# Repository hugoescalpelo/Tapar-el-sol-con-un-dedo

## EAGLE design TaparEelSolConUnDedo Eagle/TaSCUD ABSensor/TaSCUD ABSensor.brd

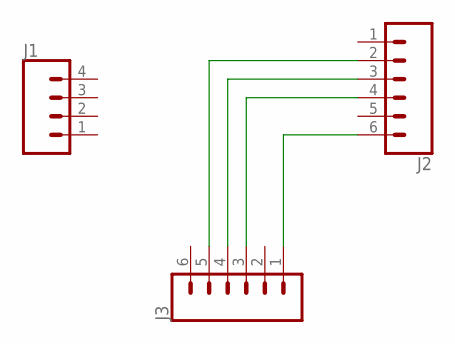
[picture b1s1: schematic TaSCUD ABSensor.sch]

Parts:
J1: CONN_04LONGPADS; 1X04_LONGPADS
J2, J3: CONN_06LONGPADS; 1X06_LONGPADS

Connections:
unnamed: J2.6, J3.1
unnamed: J2.4, J3.3
unnamed: J2.3, J3.4
unnamed: J2.2, J3.5

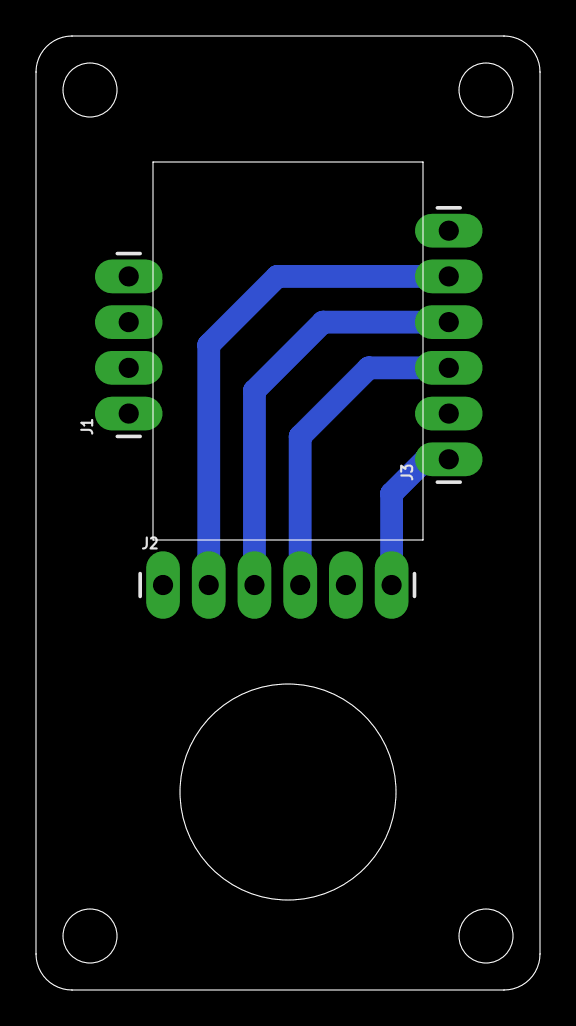
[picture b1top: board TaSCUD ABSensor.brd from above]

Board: 2 copper layers, 28.0 x 53.0 mm, 3 parts (0 on the bottom side), 4 nets.

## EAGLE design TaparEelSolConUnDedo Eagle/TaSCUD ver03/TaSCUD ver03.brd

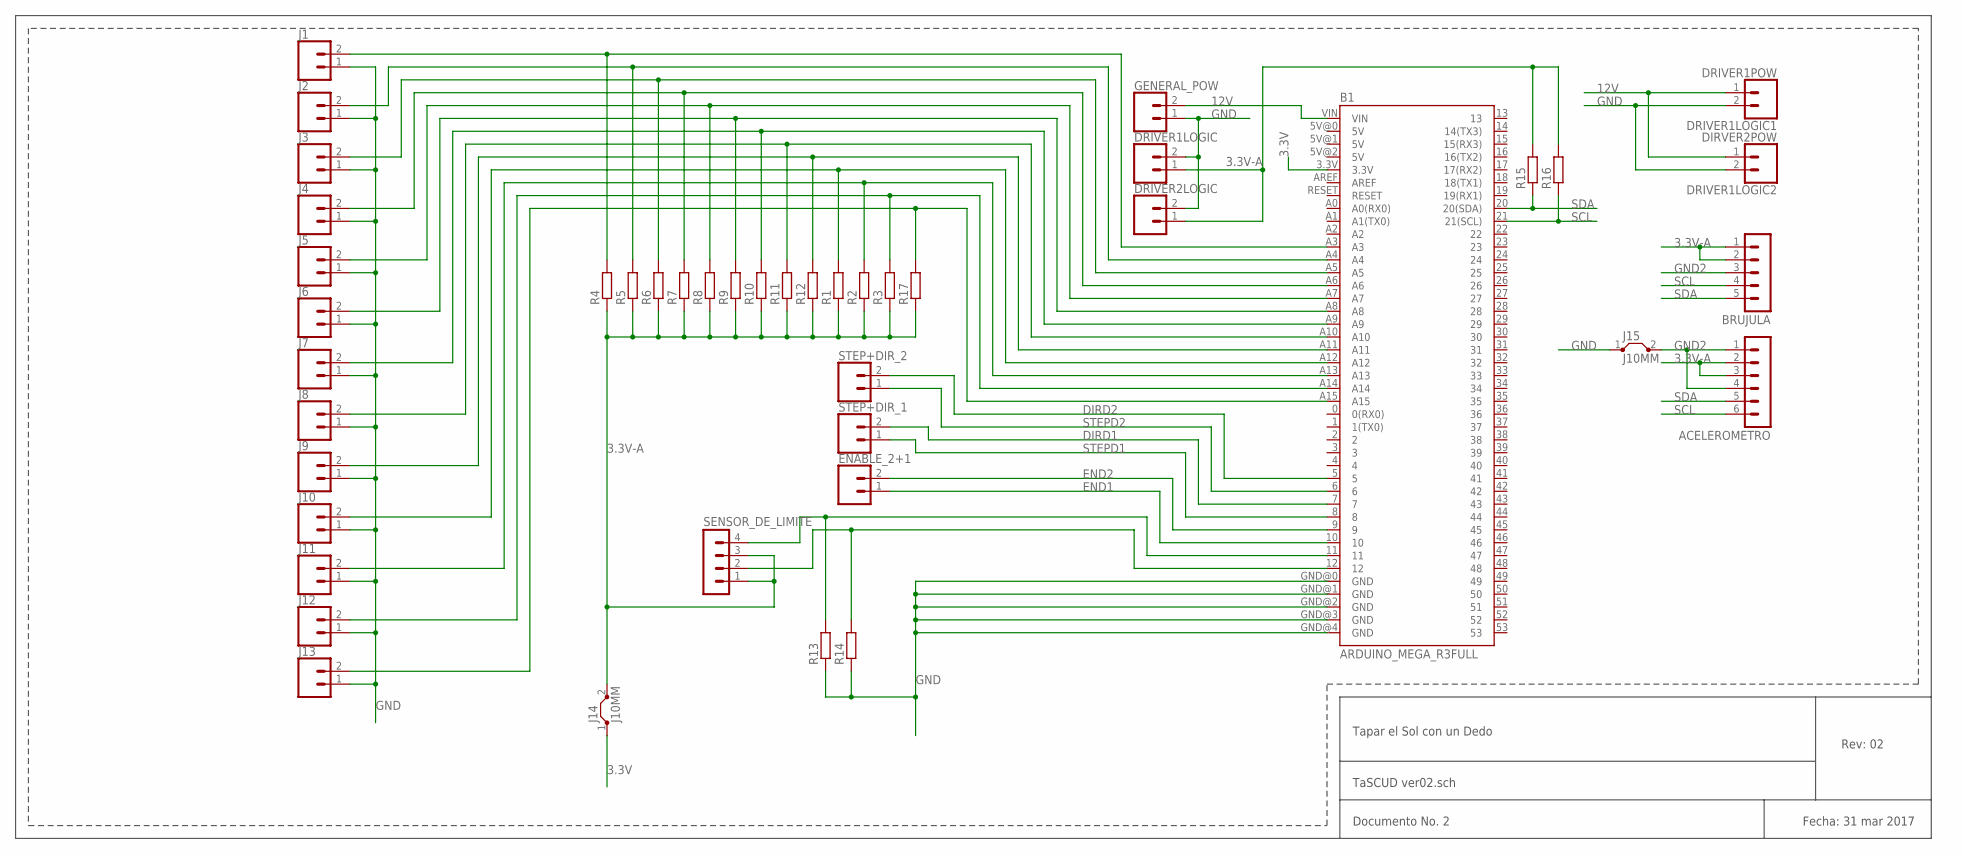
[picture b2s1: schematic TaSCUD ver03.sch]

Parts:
ACELEROMETRO: MA06-1
B1: ARDUINO_MEGA_R3FULL; ARDUINO_MEGA
BRUJULA: MA05-1
DRIVER1LOGIC, DRIVER2LOGIC: CONN_023.5MM-NO_SILK; SCREWTERMINAL-3.5MM-2-NS
DRIVER1LOGIC1: DRIVER1POW; SCREWTERMINAL-3.5MM-2-NS
DRIVER1LOGIC2: DIRVER2POW; SCREWTERMINAL-3.5MM-2-NS
ENABLE_2+1: CONN_023.5MM-NO_SILK; SCREWTERMINAL-3.5MM-2-NS
GENERAL_POW: CONN_023.5MM-NO_SILK; SCREWTERMINAL-3.5MM-2-NS
J1, J2, J3, J4, J5, J6, J7, J8, J9, J10, J11, J12, J13: CONN_023.5MM-NO_SILK; SCREWTERMINAL-3.5MM-2-NS
J14, J15: J10MM; 10
R1, R2, R3, R4, R5, R6, R7, R8, R9, R10, R11, R12, R13, R14, R15, R16, R17: R-EU_0204/7; 0204/7
SENSOR_DE_LIMITE: MA04-1
STEP+DIR_1, STEP+DIR_2: CONN_023.5MM-NO_SILK; SCREWTERMINAL-3.5MM-2-NS

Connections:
3.3V: B1.3.3V, J14.1
3.3V-A: ACELEROMETRO.2, ACELEROMETRO.3, BRUJULA.1, BRUJULA.2, DRIVER1LOGIC.1, DRIVER2LOGIC.1, J14.2, R1.1, R2.1, R3.1, R4.1, R5.1, R6.1, R7.1, R8.1, R9.1, R10.1, R11.1, R12.1, R15.2, R16.2, R17.1, SENSOR_DE_LIMITE.1, SENSOR_DE_LIMITE.3
12V: B1.VIN, DRIVER1LOGIC1.1, DRIVER1LOGIC2.1, GENERAL_POW.2
DIRD1: B1.7, STEP+DIR_1.2
DIRD2: B1.5, STEP+DIR_2.2
END1: B1.10, ENABLE_2+1.1
END2: B1.9, ENABLE_2+1.2
GND: B1.GND@0 (GND), B1.GND@1 (GND), B1.GND@2 (GND), B1.GND@3 (GND), B1.GND@4 (GND), DRIVER1LOGIC.2, DRIVER1LOGIC1.2, DRIVER1LOGIC2.2, DRIVER2LOGIC.2, GENERAL_POW.1, J1.1, J2.1, J3.1, J4.1, J5.1, J6.1, J7.1, J8.1, J9.1, J10.1, J11.1, J12.1, J13.1, J15.1, R13.1, R14.1
GND2: ACELEROMETRO.1, ACELEROMETRO.4, BRUJULA.3, J15.2
unnamed: B1.A12, J10.2, R1.2
unnamed: B1.A13, J11.2, R2.2
unnamed: B1.A14, J12.2, R3.2
unnamed: B1.A15, J13.2, R17.2
unnamed: B1.A3, J1.2, R4.2
unnamed: B1.11, R13.2, SENSOR_DE_LIMITE.4
unnamed: B1.A4, J2.2, R5.2
unnamed: B1.A5, J3.2, R6.2
unnamed: B1.A6, J4.2, R7.2
unnamed: B1.A7, J5.2, R8.2
unnamed: B1.A8, J6.2, R9.2
unnamed: B1.A9, J7.2, R10.2
unnamed: B1.A10, J8.2, R11.2
unnamed: B1.A11, J9.2, R12.2
unnamed: B1.12, R14.2, SENSOR_DE_LIMITE.2
SCL: ACELEROMETRO.6, B1.21 (21(SCL)), BRUJULA.4, R16.1
SDA: ACELEROMETRO.5, B1.20 (20(SDA)), BRUJULA.5, R15.1
STEPD1: B1.8, STEP+DIR_1.1
STEPD2: B1.6, STEP+DIR_2.1

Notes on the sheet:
Tapar el Sol con un Dedo
TaSCUD ver02.sch
Documento No. 2
Fecha: 31 mar 2017
Rev: 02

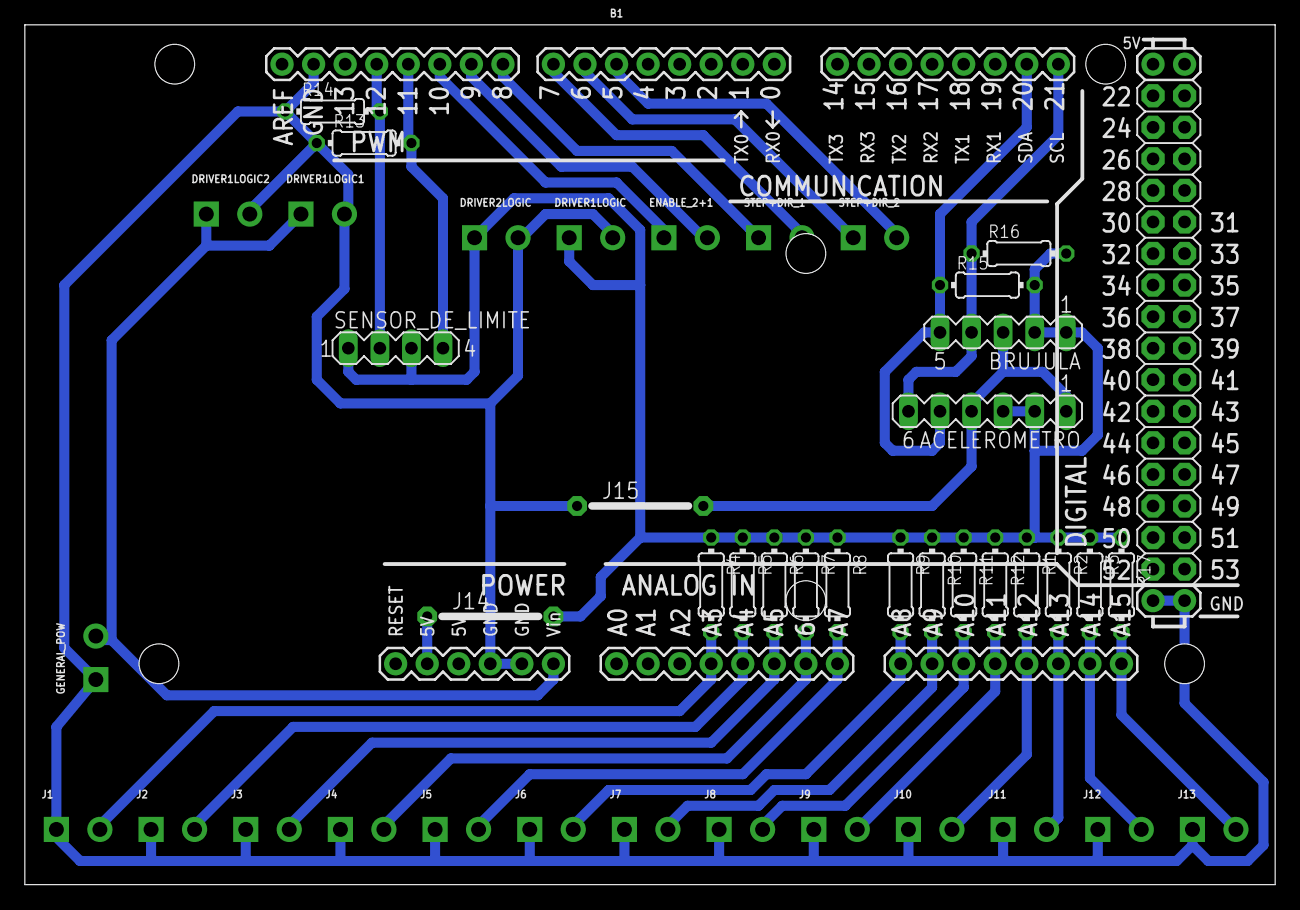
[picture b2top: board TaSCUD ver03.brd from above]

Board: 2 copper layers, 100.6 x 69.2 mm, 44 parts (0 on the bottom side), 28 nets.

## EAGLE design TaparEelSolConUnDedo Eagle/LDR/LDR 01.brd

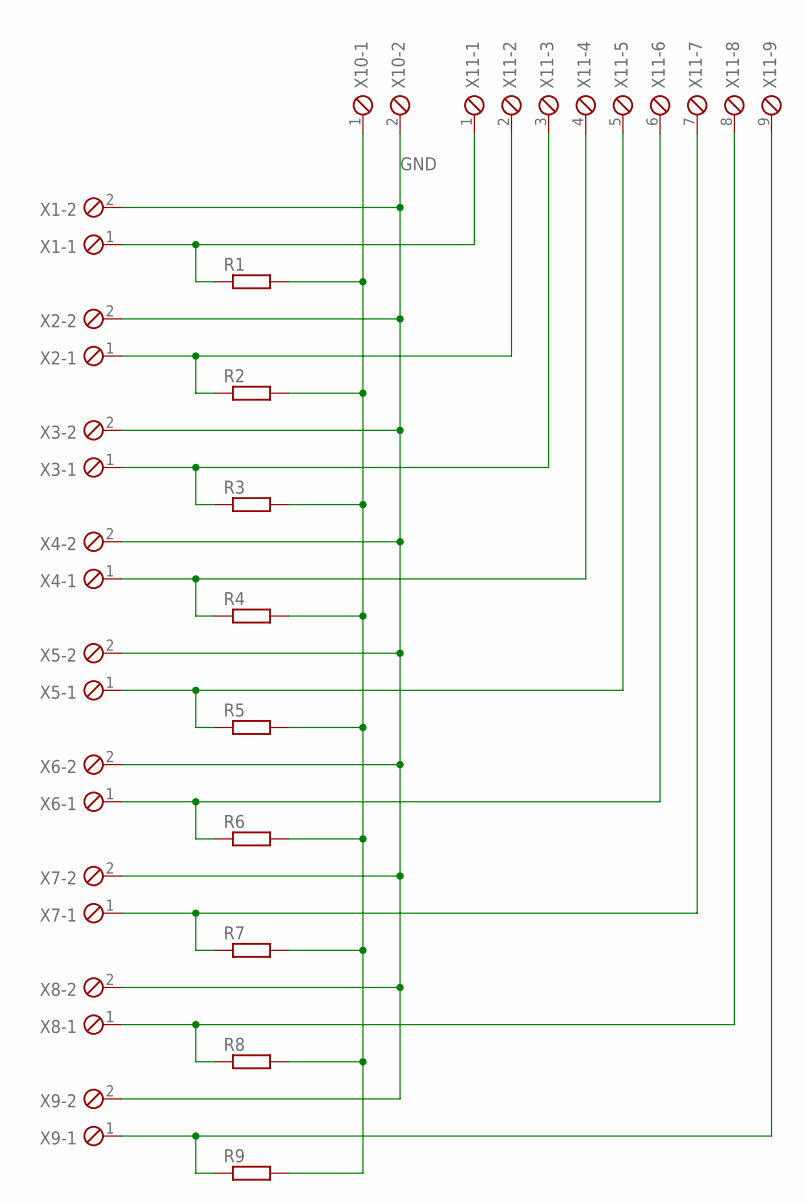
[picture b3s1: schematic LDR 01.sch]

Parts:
R1, R2, R3, R4, R5, R6, R7, R8, R9: R-EU_0204/7; 0204/7
X1, X2, X3, X4, X5, X6, X7, X8, X9, X10: MPT2; 2POL254
X11: MPT9; 9POL254

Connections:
GND: X1.2, X2.2, X3.2, X4.2, X5.2, X6.2, X7.2, X8.2, X9.2, X10.2
unnamed: R1.2, R2.2, R3.2, R4.2, R5.2, R6.2, R7.2, R8.2, R9.2, X10.1
unnamed: R1.1, X1.1, X11.1
unnamed: R2.1, X2.1, X11.2
unnamed: R3.1, X3.1, X11.3
unnamed: R4.1, X4.1, X11.4
unnamed: R5.1, X5.1, X11.5
unnamed: R6.1, X6.1, X11.6
unnamed: R7.1, X7.1, X11.7
unnamed: R8.1, X8.1, X11.8
unnamed: R9.1, X9.1, X11.9

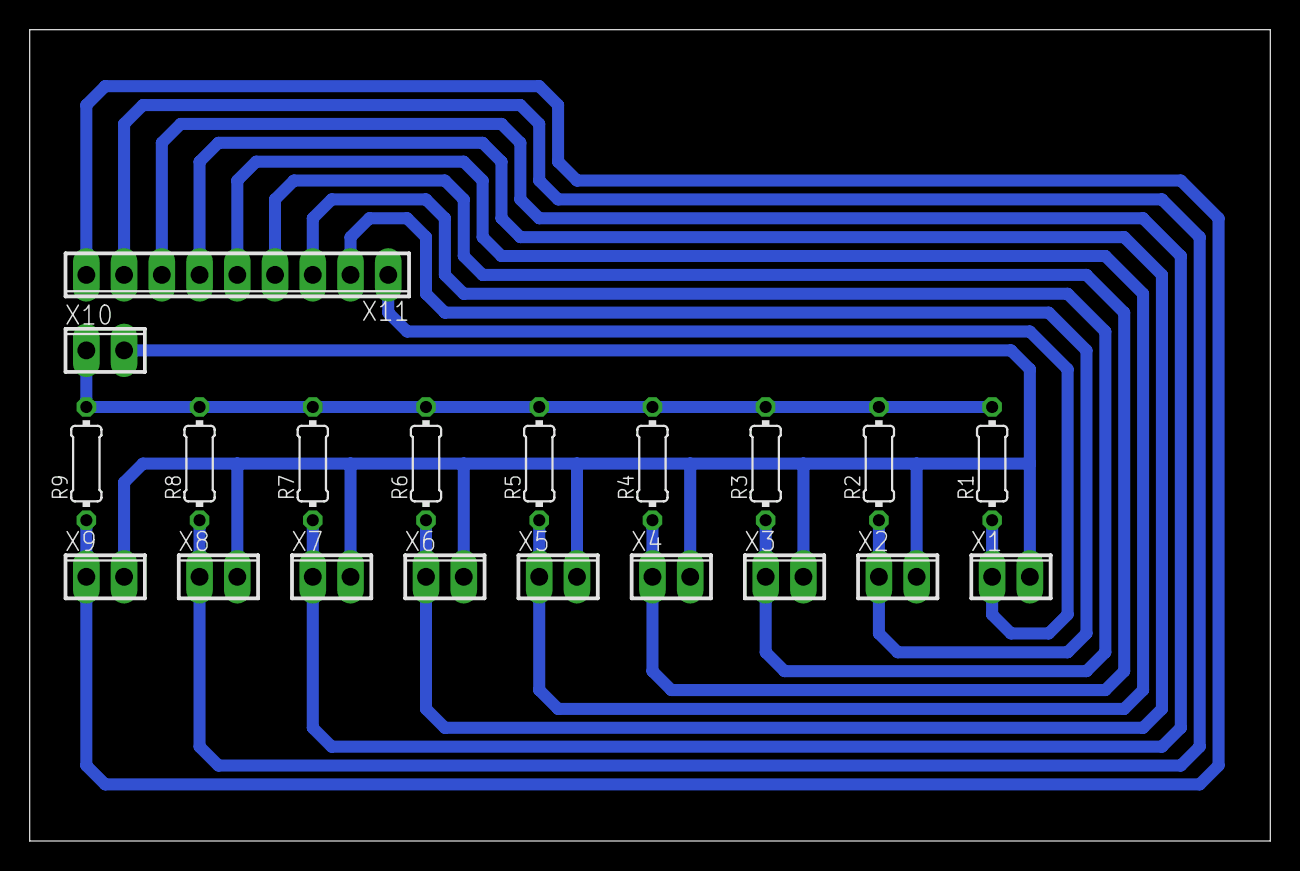
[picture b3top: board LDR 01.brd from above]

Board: 2 copper layers, 83.5 x 54.6 mm, 20 parts (0 on the bottom side), 11 nets.

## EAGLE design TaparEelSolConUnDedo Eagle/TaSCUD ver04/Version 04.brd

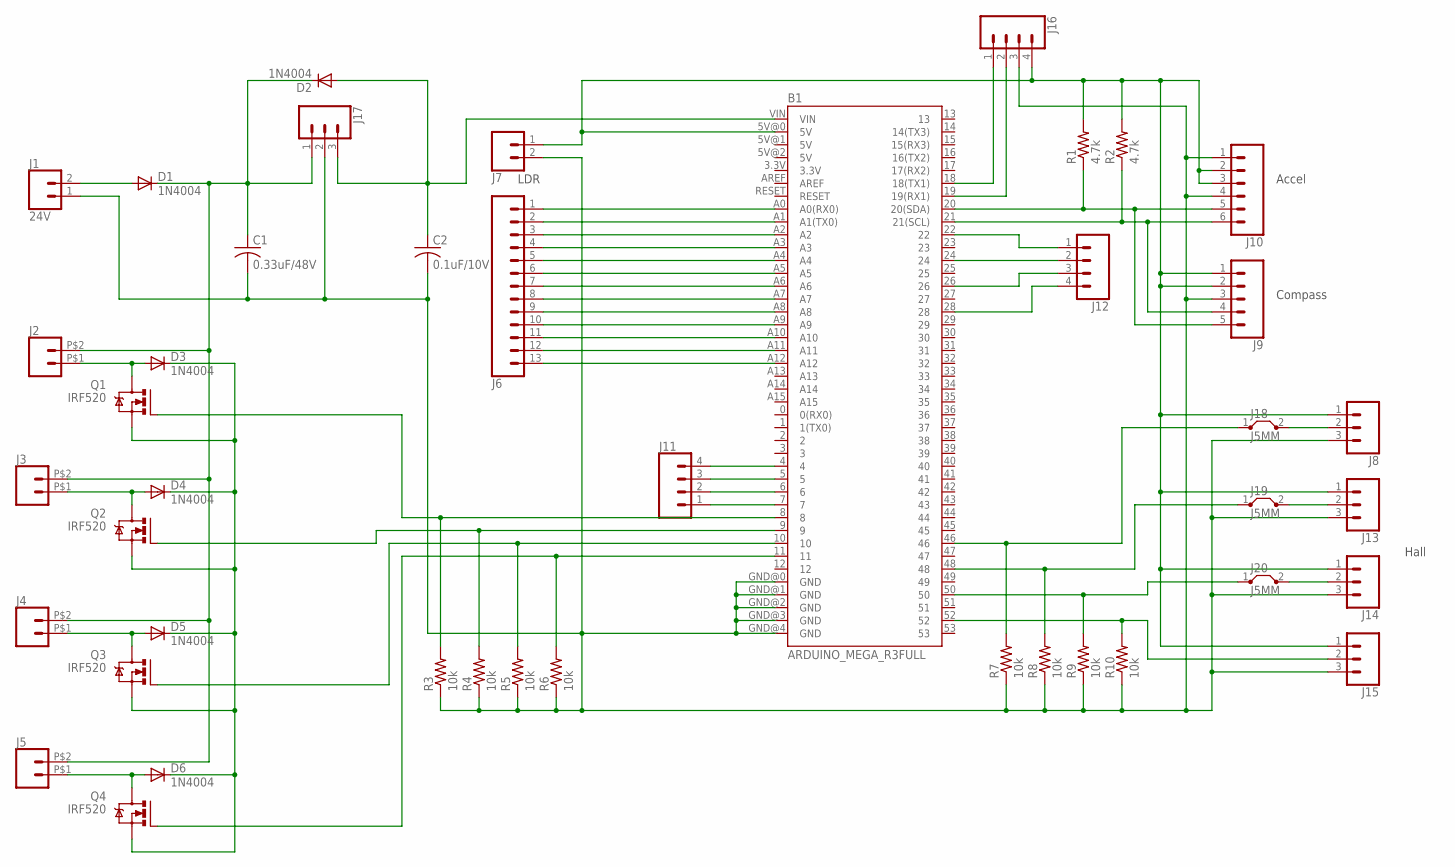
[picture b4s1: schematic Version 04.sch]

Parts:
B1: ARDUINO_MEGA_R3FULL; ARDUINO_MEGA
C1: 0.33uF/48V; C050-075X075
C2: 0.1uF/10V; C025-060X050
D1, D2, D3, D4, D5, D6: 1N4004; DO41-10
J1: 24V; SCREWTERMINAL-3.5MM-2_LOCK
J2, J3, J4, J5: CONN_02PTH2; 1X02_BIG
J6: CONN_13LONGPADS; 1X13-LONGPADS
J7: CONN_02LOCK_LONGPADS; 1X02_LOCK_LONGPADS
J8, J13, J14, J15, J17: CONN_03LONGPADS; 1X03_LONGPADS
J9: CONN_05PTH_LONGPADS; 1X05_LONGPADS
J10: CONN_06LONGPADS; 1X06_LONGPADS
J11, J12, J16: CONN_04LONGPADS; 1X04_LONGPADS
J18, J19, J20: J5MM; 05
Q1, Q2, Q3, Q4: IRF520; TO220BV
R1, R2: 4.7k; 0207/7
R3, R4, R5, R6, R7, R8, R9, R10: 10k; 0207/10

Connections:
5V: B1.VIN, C2.1, D2.A, J17.3
5VR: B1.5V@0 (5V), J7.1, J8.1, J9.1, J9.2, J10.2, J10.3, J13.1, J14.1, J15.1, J16.4, R1.2, R2.2
24V: D1.A, J1.2
24VD: C1.1, D1.C, D2.C, J2.P$2 (2), J3.P$2 (2), J4.P$2 (2), J5.P$2 (2), J17.1
GND: B1.GND@0 (GND), B1.GND@1 (GND), B1.GND@2 (GND), B1.GND@3 (GND), B1.GND@4 (GND), C1.2, C2.2, J1.1, J7.2, J8.3, J9.3, J10.1, J10.4, J13.3, J14.3, J15.3, J16.3, J17.2, R3.1, R4.1, R5.1, R6.1, R7.1, R8.1, R9.1, R10.1
unnamed: B1.A0 (A0(RX0)), J6.1
unnamed: B1.A1 (A1(TX0)), J6.2
unnamed: B1.A2, J6.3
unnamed: B1.A3, J6.4
unnamed: B1.A4, J6.5
unnamed: B1.A5, J6.6
unnamed: B1.A6, J6.7
unnamed: B1.A7, J6.8
unnamed: B1.A8, J6.9
unnamed: B1.A9, J6.10
unnamed: B1.A10, J6.11
unnamed: B1.A11, J6.12
unnamed: B1.A12, J6.13
unnamed: B1.52, J15.2, R10.2
unnamed: B1.50, J20.1, R9.2
unnamed: B1.48, J19.1, R8.2
unnamed: B1.46, J18.1, R7.2
unnamed: B1.21 (21(SCL)), J9.4, J10.6, R2.1
unnamed: B1.22, J12.1
unnamed: B1.24, J12.2
unnamed: B1.4, J11.4
unnamed: B1.5, J11.3
unnamed: B1.6, J11.2
unnamed: B1.7, J11.1
unnamed: B1.26, J12.3
unnamed: B1.28, J12.4
unnamed: D3.A, J2.P$1 (1), Q1.D
unnamed: D4.A, J3.P$1 (1), Q2.D
unnamed: D5.A, J4.P$1 (1), Q3.D
unnamed: D6.A, J5.P$1 (1), Q4.D
unnamed: D3.C, D4.C, D5.C, D6.C, Q1.S, Q2.S, Q3.S, Q4.S
unnamed: B1.19 (19(RX1)), J16.2
unnamed: B1.18 (18(TX1)), J16.1
unnamed: B1.8, Q1.G, R3.2
unnamed: B1.9, Q2.G, R4.2
unnamed: B1.10, Q3.G, R5.2
unnamed: B1.11, Q4.G, R6.2
unnamed: J14.2, J20.2
unnamed: J13.2, J19.2
unnamed: J8.2, J18.2
SDA: B1.20 (20(SDA)), J9.5, J10.5, R1.1

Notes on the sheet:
Hall
LDR
Compass
Accel

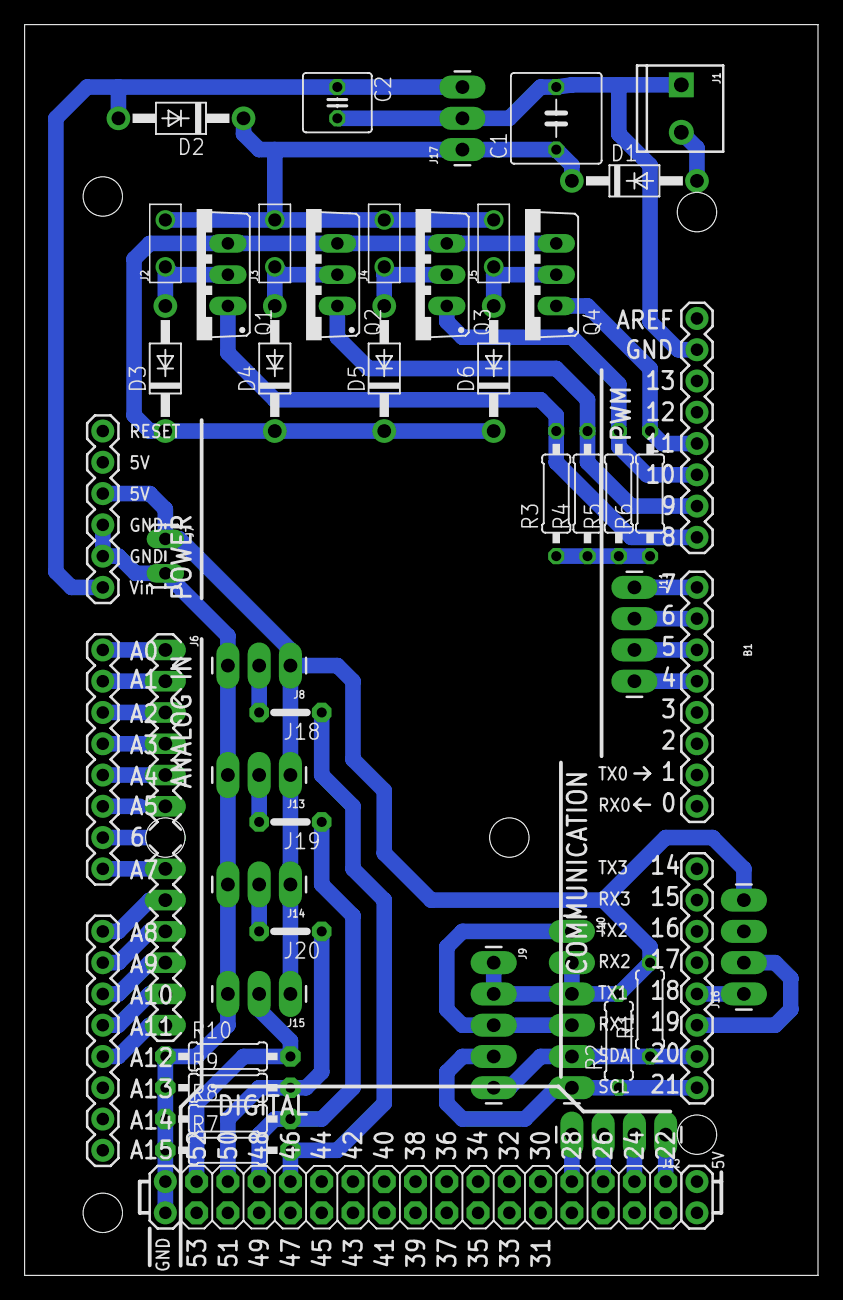
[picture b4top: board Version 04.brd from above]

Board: 2 copper layers, 64.4 x 101.6 mm, 43 parts (0 on the bottom side), 46 nets.

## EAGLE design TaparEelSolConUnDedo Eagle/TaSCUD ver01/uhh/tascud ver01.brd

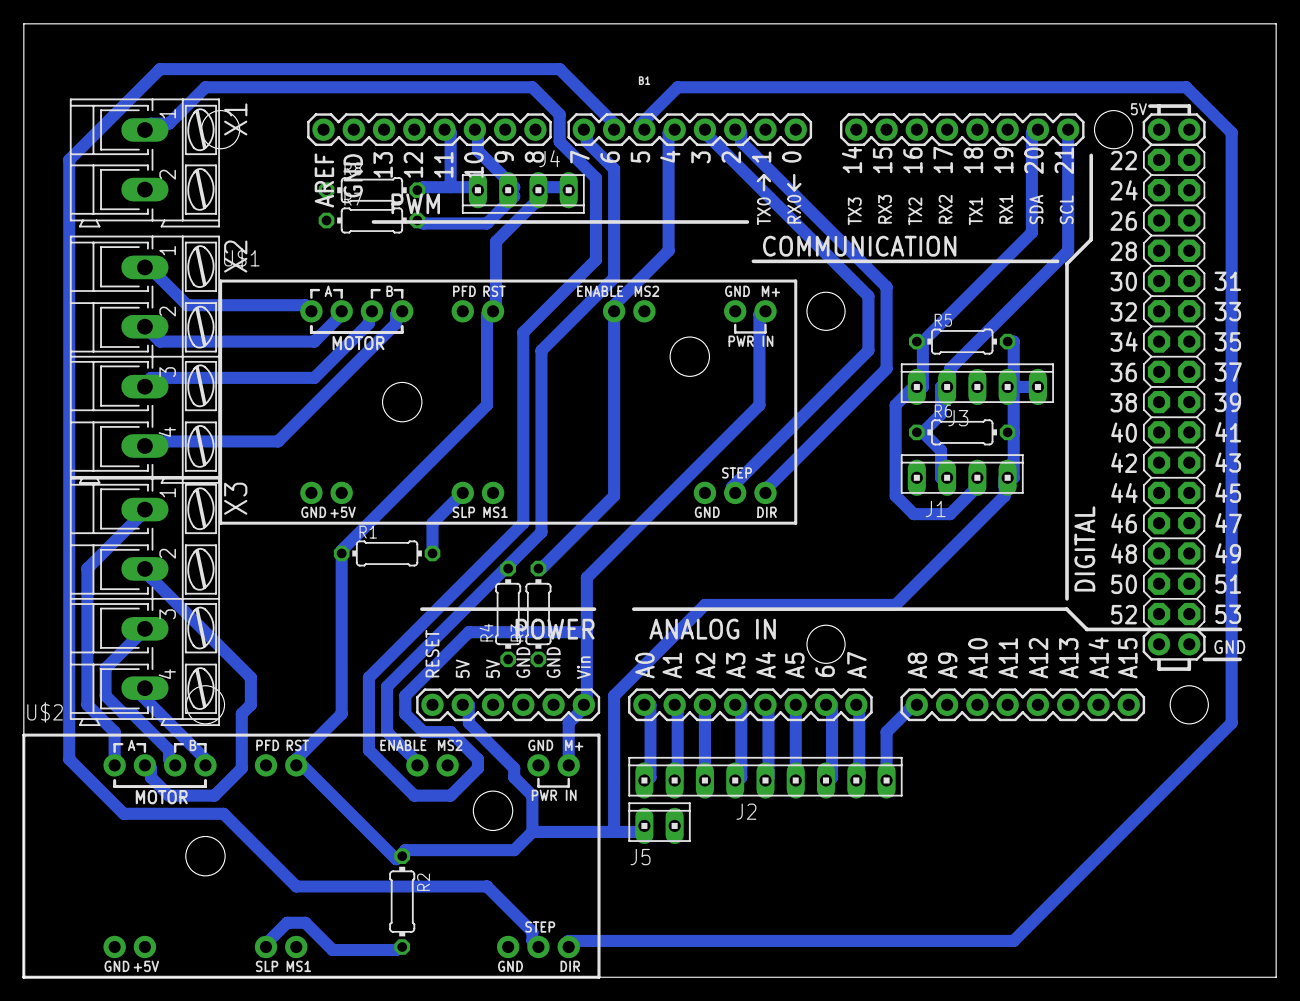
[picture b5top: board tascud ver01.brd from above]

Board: 2 copper layers, 105.1 x 80.0 mm, 19 parts (0 on the bottom side), 31 nets.

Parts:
B1: ARDUINO_MEGA_R3FULL; ARDUINO_MEGA
J1, J4: 10X04MTA
J2: 10X09MTA
J3: 10X05MTA
J5: 10X02MTA
R1, R2, R3, R4, R5, R6, R7, R8: 1k; 0204/7
U$1, U$2: EASYDRIVER_V44
X1: AK300/2
X2, X3: AK300/4

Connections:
3.3V: B1.3.3V, J1.1, J3.1, J3.2, J4.3, J4.4, J5.2, R1.1, R2.1, R5.2, R6.2, U$1.RST, U$2.RST
12V: B1.VIN, U$1.M+, U$2.M+, X1.1
unnamed: B1.2, U$1.DIR
unnamed: B1.4, R3.2, U$1.ENABLE
unnamed: B1.5, U$2.DIR
unnamed: B1.6, U$2.STEP
unnamed: B1.7, R4.2, U$2.ENABLE
unnamed: B1.A1, J2.8
unnamed: B1.A2, J2.7
unnamed: U$1.A1, X2.1
unnamed: U$1.A2, X2.2
unnamed: U$1.B2, X2.3
unnamed: U$1.B1, X2.4
unnamed: U$2.A1, X3.1
unnamed: U$2.A2, X3.2
unnamed: U$2.B2, X3.3
unnamed: U$2.B1, X3.4
unnamed: B1.3, U$1.STEP
unnamed: B1.A7, J2.2
unnamed: R2.2, U$2.SLEEP
unnamed: R1.2, U$1.SLEEP
unnamed: B1.A3, J2.6
unnamed: B1.11, J4.1, R8.2
unnamed: B1.A8, J2.1
unnamed: B1.A4, J2.5
unnamed: B1.A5, J2.4
unnamed: B1.A0, J2.9
unnamed: B1.A6, J2.3
unnamed: B1.10, J4.2, R7.2
SCL: B1.21, J1.3, J3.4, R6.1
SDA: B1.20, J1.2, J3.5, R5.1

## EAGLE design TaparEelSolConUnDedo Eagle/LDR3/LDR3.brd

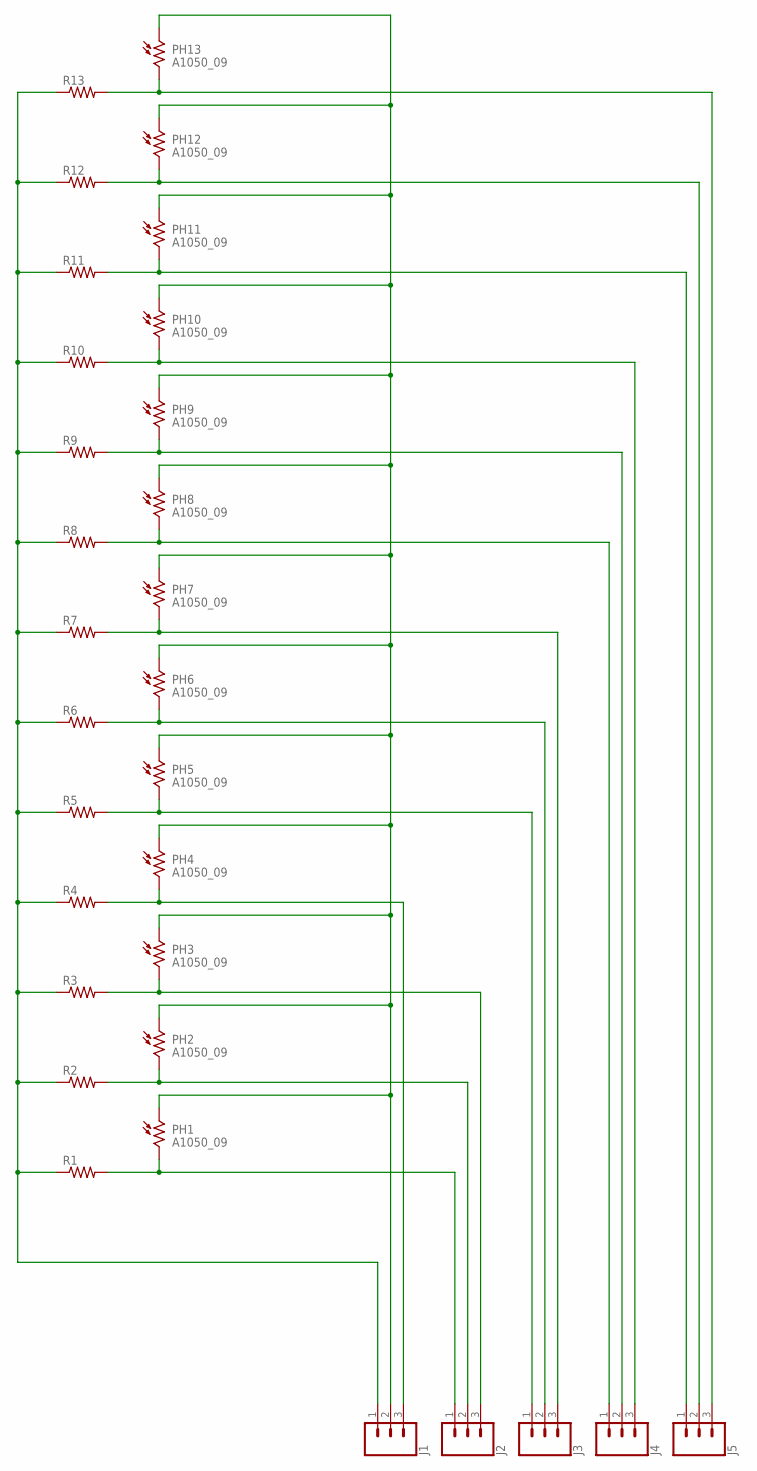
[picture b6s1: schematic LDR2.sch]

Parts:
J1, J2, J3, J4, J5: CONN_03LONGPADS; 1X03_LONGPADS
PH1, PH2, PH3, PH4, PH5, PH6, PH7, PH8, PH9, PH10, PH11, PH12, PH13: A1050_09; T0-46-A10XX
R1, R2, R3, R4, R5, R6, R7, R8, R9, R10, R11, R12, R13: R-US_0204/7; 0204/7

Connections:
5V: J1.1, R1.1, R2.1, R3.1, R4.1, R5.1, R6.1, R7.1, R8.1, R9.1, R10.1, R11.1, R12.1, R13.1
GND: J1.2, PH1.1, PH2.1, PH3.1, PH4.1, PH5.1, PH6.1, PH7.1, PH8.1, PH9.1, PH10.1, PH11.1, PH12.1, PH13.1
unnamed: J2.1, PH1.2, R1.2
unnamed: J2.2, PH2.2, R2.2
unnamed: J2.3, PH3.2, R3.2
unnamed: J1.3, PH4.2, R4.2
unnamed: J3.1, PH5.2, R5.2
unnamed: J3.2, PH6.2, R6.2
unnamed: J3.3, PH7.2, R7.2
unnamed: J4.1, PH8.2, R8.2
unnamed: J4.2, PH9.2, R9.2
unnamed: J4.3, PH10.2, R10.2
unnamed: J5.1, PH11.2, R11.2
unnamed: J5.2, PH12.2, R12.2
unnamed: J5.3, PH13.2, R13.2

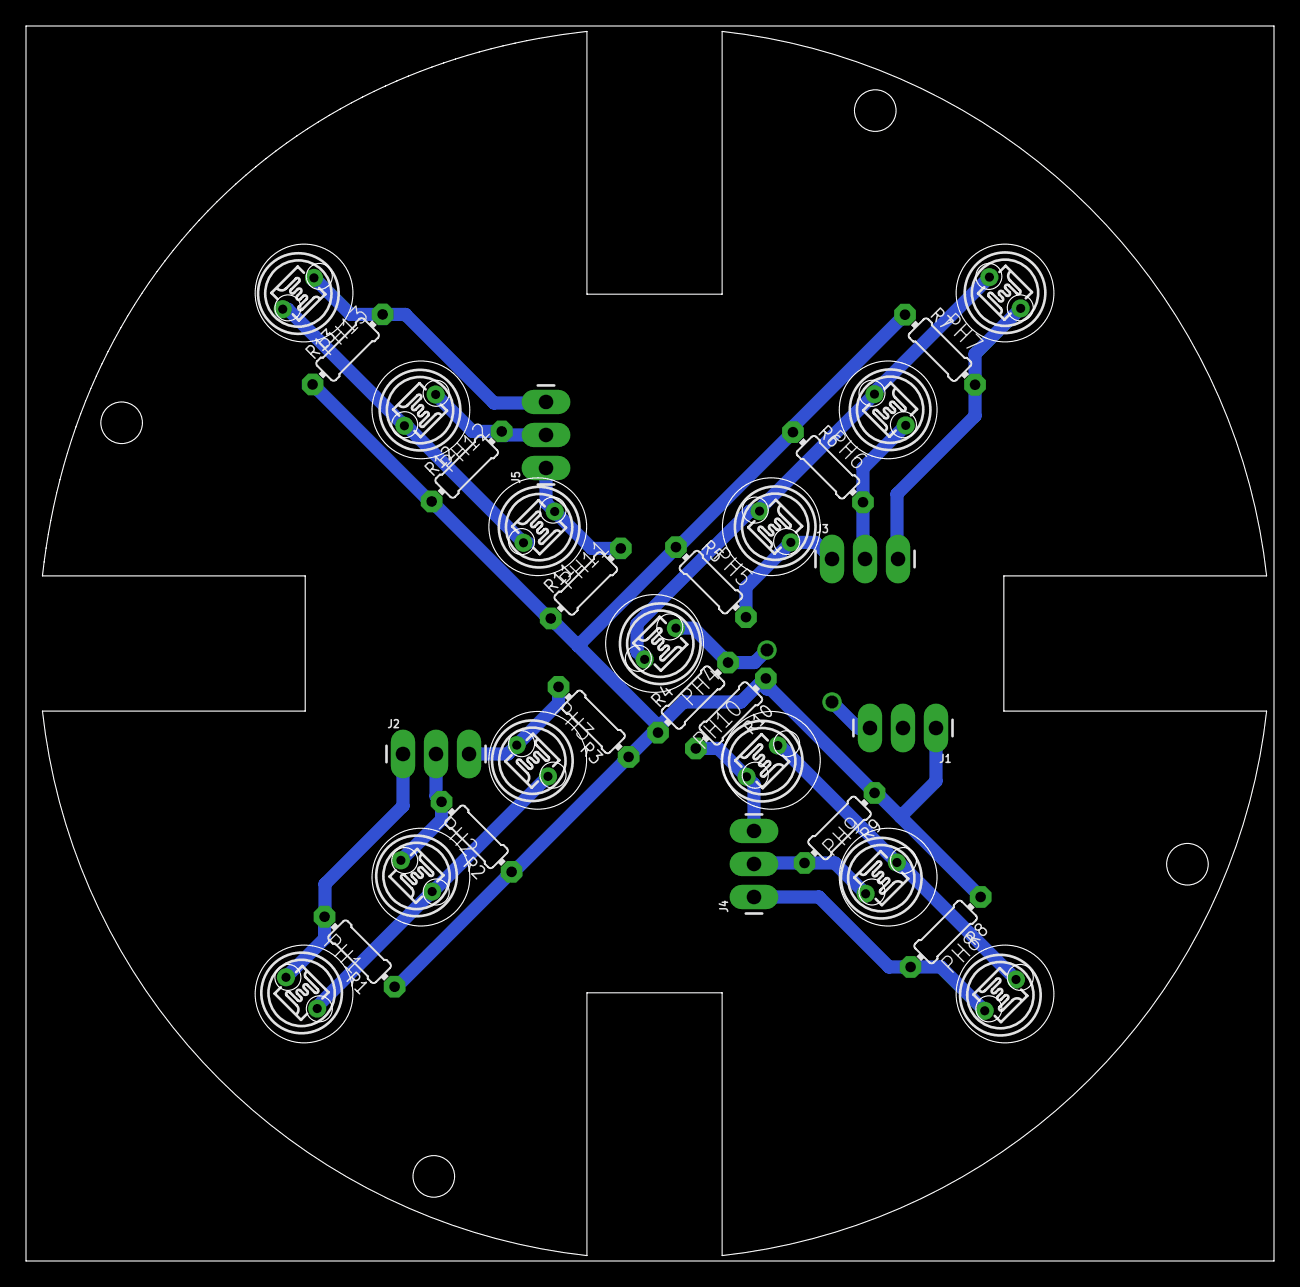
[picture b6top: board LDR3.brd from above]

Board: 2 copper layers, 96.0 x 95.0 mm, 31 parts (0 on the bottom side), 15 nets.

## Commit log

2018-07-06 Late registry
    This is not version 6 of overal arduino code, its lice 50. This project was done on july 2017.
2018-07-12 New Version Added
    Its like version 54. Just rewriting a component at a time
2018-07-12 Test sequence added
    Untested
2018-07-12 dirve added
2018-07-13 Menu added
    BT menu added. Untested
2018-07-26 Lots of files adapted
2018-08-02 Test sequence tested
    Motor direction fixed
2018-08-03 Toggle enable Motors Added
    Terminanton condition for running sequence fixed
2018-08-03 Azimuth movements tested
2018-08-03 Altitud motors tested
2018-08-06 Cutted parts
2018-08-13 ABSensor Holder

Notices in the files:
parts and their libraries:
SparkFun-Connectors: Licensing: Creative Commons ShareAlike 4.0 International - https://creativecommons.org/licenses/by-sa/4.0
